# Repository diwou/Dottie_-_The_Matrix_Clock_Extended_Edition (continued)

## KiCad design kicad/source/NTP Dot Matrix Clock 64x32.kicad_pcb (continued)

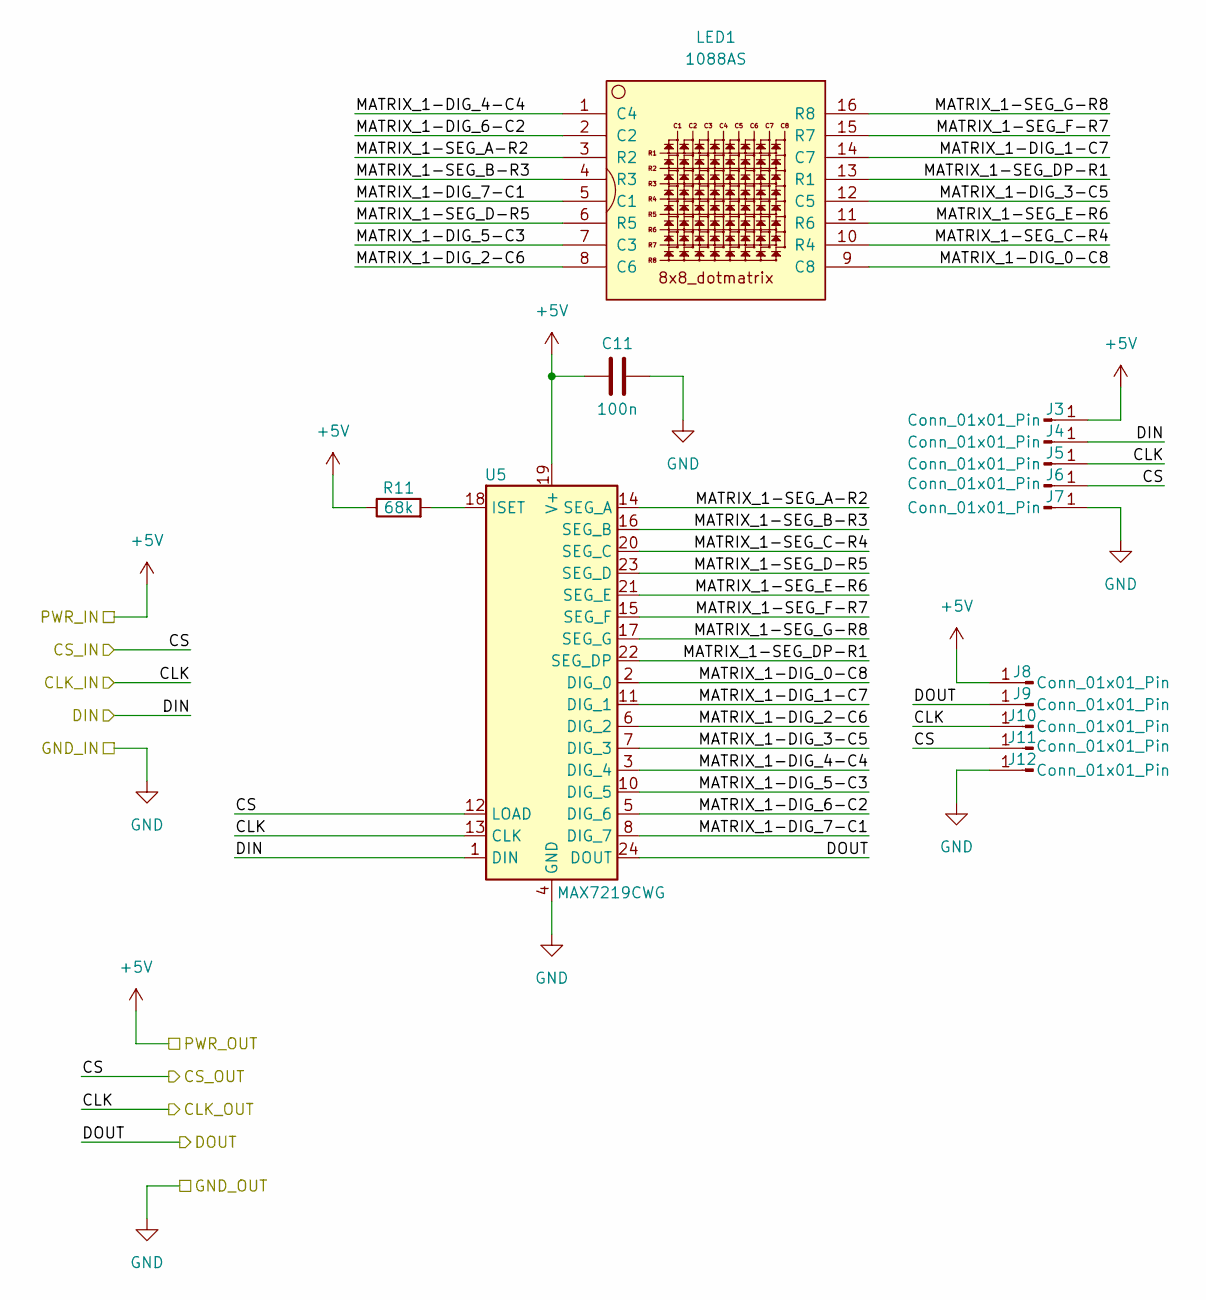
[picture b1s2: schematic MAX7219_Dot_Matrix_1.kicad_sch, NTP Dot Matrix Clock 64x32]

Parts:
C11: 100n; C_0805_2012Metric_Pad1.18x1.45mm_HandSolder
J3, J4, J5, J6, J7, J8, J9, J10, J11, J12: Conn_01x01_Pin; TestPoint_Pad_1.5x1.5mm
LED1: 1088AS; LED_1088_Pin_Header
R11: 68k; R_0805_2012Metric_Pad1.20x1.40mm_HandSolder
U5: MAX7219CWG; SOIC-24W_7.5x15.4mm_P1.27mm

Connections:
+5V: C11.1, J3.1 (Pin_1_1), J8.1 (Pin_1_1), R11.1, U5.19 (V+); also elsewhere on the board
/MAX7219 Dot Matrix 1/DOUT: J9.1 (Pin_1_1), U5.24 (DOUT); also elsewhere on the board
/MAX7219 Dot Matrix 1/MATRIX_1-DIG_0-C8: LED1.9 (C8), U5.2 (DIG_0)
/MAX7219 Dot Matrix 1/MATRIX_1-DIG_1-C7: LED1.14 (C7), U5.11 (DIG_1)
/MAX7219 Dot Matrix 1/MATRIX_1-DIG_2-C6: LED1.8 (C6), U5.6 (DIG_2)
/MAX7219 Dot Matrix 1/MATRIX_1-DIG_3-C5: LED1.12 (C5), U5.7 (DIG_3)
/MAX7219 Dot Matrix 1/MATRIX_1-DIG_4-C4: LED1.1 (C4), U5.3 (DIG_4)
/MAX7219 Dot Matrix 1/MATRIX_1-DIG_5-C3: LED1.7 (C3), U5.10 (DIG_5)
/MAX7219 Dot Matrix 1/MATRIX_1-DIG_6-C2: LED1.2 (C2), U5.5 (DIG_6)
/MAX7219 Dot Matrix 1/MATRIX_1-DIG_7-C1: LED1.5 (C1), U5.8 (DIG_7)
/MAX7219 Dot Matrix 1/MATRIX_1-SEG_A-R2: LED1.3 (R2), U5.14 (SEG_A)
/MAX7219 Dot Matrix 1/MATRIX_1-SEG_B-R3: LED1.4 (R3), U5.16 (SEG_B)
/MAX7219 Dot Matrix 1/MATRIX_1-SEG_C-R4: LED1.10 (R4), U5.20 (SEG_C)
/MAX7219 Dot Matrix 1/MATRIX_1-SEG_D-R5: LED1.6 (R5), U5.23 (SEG_D)
/MAX7219 Dot Matrix 1/MATRIX_1-SEG_DP-R1: LED1.13 (R1), U5.22 (SEG_DP)
/MAX7219 Dot Matrix 1/MATRIX_1-SEG_E-R6: LED1.11 (R6), U5.21 (SEG_E)
/MAX7219 Dot Matrix 1/MATRIX_1-SEG_F-R7: LED1.15 (R7), U5.15 (SEG_F)
/MAX7219 Dot Matrix 1/MATRIX_1-SEG_G-R8: LED1.16 (R8), U5.17 (SEG_G)
CLK: J5.1 (Pin_1_1), J10.1 (Pin_1_1), U5.13 (CLK); also elsewhere on the board
CS: J6.1 (Pin_1_1), J11.1 (Pin_1_1), U5.12 (LOAD); also elsewhere on the board
DIN: J4.1 (Pin_1_1), U5.1 (DIN); also elsewhere on the board
GND: C11.2, J7.1 (Pin_1_1), J12.1 (Pin_1_1), U5.4 (GND), U5.9 (GND); also elsewhere on the board
unnamed: R11.2, U5.18 (ISET)

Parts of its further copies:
C12, C13, C14, C15, C16, C17, C18, C19, C20, C21, C22, C23, C24, C25, C26, C27, C28, C29, C30, C31, C32, C33, C34: 100n; C_0805_2012Metric_Pad1.18x1.45mm_HandSolder
J13, J14, J15, J16, J17, J18, J19, J20, J21, J22, J23, J24, J25, J26, J27, J28, J29, J30, J31, J32, J33, J34, J35, J36, J37, J38, J39, J40, J41, J42, J43, J44, J45, J46, J47, J48, J49, J50, J51, J52, J53, J54, J55, J56, J57, J58, J59, J60, J61, J62, J63, J64, J65, J66, J67, J68, J69, J70, J71, J72, J73, J74, J75, J76, J77, J78, J79, J80, J81, J82, J83, J84, J85, J86, J87, J88, J89, J90, J91, J92, J93, J94, J95, J96, J97, J98, J99, J100, J101, J102, J103, J104, J105, J106, J107, J108, J109, J110, J111, J112, J113, J114, J115, J116, J117, J118, J119, J120, J121, J122, J123, J124, J125, J126, J127, J128, J129, J130, J131, J132, J133, J134, J135, J136, J137, J138, J139, J140, J141, J142, J143, J144, J145, J146, J147, J148, J149, J150, J151, J152, J153, J154, J155, J156, J157, J158, J159, J160, J161, J162, J163, J164, J165, J166, J167, J168, J169, J170, J171, J172, J173, J174, J175, J176, J177, J178, J179, J180, J181, J182, J183, J184, J185, J186, J187, J188, J189, J190, J191, J192, J193, J194, J195, J196, J197, J198, J199, J200, J201, J202, J203, J204, J205, J206, J207, J208, J209, J210, J211, J212, J213, J214, J215, J216, J217, J218, J219, J220, J221, J222, J223, J224, J225, J226, J227, J228, J229, J230, J231, J232, J233, J234, J235, J236, J237, J238, J239, J240, J241, J242: Conn_01x01_Pin; TestPoint_Pad_1.5x1.5mm
LED2, LED3, LED4, LED5, LED6, LED7, LED8, LED9, LED10, LED11, LED12, LED13, LED14, LED15, LED16, LED17, LED18, LED19, LED20, LED21, LED22, LED23, LED24: 1088AS; LED_1088_Pin_Header
R12, R13, R14, R15, R16, R17, R18, R19, R20, R21, R22, R23, R24, R25, R26, R27, R28, R29, R30, R31, R32, R33, R34: 68k; R_0805_2012Metric_Pad1.20x1.40mm_HandSolder
U6, U7, U8, U9, U10, U11, U12, U13, U14, U15, U16, U17, U18, U19, U20, U21, U22, U23, U24, U25, U26, U27, U28: MAX7219CWG; SOIC-24W_7.5x15.4mm_P1.27mm

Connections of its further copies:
+5V: C12.1, C13.1, C14.1, C15.1, C16.1, C17.1, C18.1, C19.1, C20.1, C21.1, C22.1, C23.1, C24.1, C25.1, C26.1, C27.1, C28.1, C29.1, C30.1, C31.1, C32.1, C33.1, C34.1, J13.1 (Pin_1_1), J18.1 (Pin_1_1), J23.1 (Pin_1_1), J28.1 (Pin_1_1), J33.1 (Pin_1_1), J38.1 (Pin_1_1), J43.1 (Pin_1_1), J48.1 (Pin_1_1), J53.1 (Pin_1_1), J58.1 (Pin_1_1), J63.1 (Pin_1_1), J68.1 (Pin_1_1), J73.1 (Pin_1_1), J78.1 (Pin_1_1), J83.1 (Pin_1_1), J88.1 (Pin_1_1), J93.1 (Pin_1_1), J98.1 (Pin_1_1), J103.1 (Pin_1_1), J108.1 (Pin_1_1), J113.1 (Pin_1_1), J118.1 (Pin_1_1), J123.1 (Pin_1_1), J128.1 (Pin_1_1), J133.1 (Pin_1_1), J138.1 (Pin_1_1), J143.1 (Pin_1_1), J148.1 (Pin_1_1), J153.1 (Pin_1_1), J158.1 (Pin_1_1), J163.1 (Pin_1_1), J168.1 (Pin_1_1), J173.1 (Pin_1_1), J178.1 (Pin_1_1), J183.1 (Pin_1_1), J188.1 (Pin_1_1), J193.1 (Pin_1_1), J198.1 (Pin_1_1), J203.1 (Pin_1_1), J208.1 (Pin_1_1), J213.1 (Pin_1_1), J218.1 (Pin_1_1), J223.1 (Pin_1_1), J228.1 (Pin_1_1), J233.1 (Pin_1_1), J238.1 (Pin_1_1), R12.1, R13.1, R14.1, R15.1, R16.1, R17.1, R18.1, R19.1, R20.1, R21.1, R22.1, R23.1, R24.1, R25.1, R26.1, R27.1, R28.1, R29.1, R30.1, R31.1, R32.1, R33.1, R34.1, U6.19 (V+), U7.19 (V+), U8.19 (V+)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; also elsewhere on the board
/MAX7219 Dot Matrix 1/DOUT: J14.1 (Pin_1_1), U6.1 (DIN); also elsewhere on the board
/MAX7219 Dot Matrix 2/DOUT: J19.1 (Pin_1_1), J24.1 (Pin_1_1), U6.24 (DOUT), U7.1 (DIN)
/MAX7219 Dot Matrix 2/MATRIX_1-DIG_0-C8: LED2.9 (C8), U6.2 (DIG_0)
/MAX7219 Dot Matrix 2/MATRIX_1-DIG_1-C7: LED2.14 (C7), U6.11 (DIG_1)
/MAX7219 Dot Matrix 2/MATRIX_1-DIG_2-C6: LED2.8 (C6), U6.6 (DIG_2)
/MAX7219 Dot Matrix 2/MATRIX_1-DIG_3-C5: LED2.12 (C5), U6.7 (DIG_3)
/MAX7219 Dot Matrix 2/MATRIX_1-DIG_4-C4: LED2.1 (C4), U6.3 (DIG_4)
/MAX7219 Dot Matrix 2/MATRIX_1-DIG_5-C3: LED2.7 (C3), U6.10 (DIG_5)
/MAX7219 Dot Matrix 2/MATRIX_1-DIG_6-C2: LED2.2 (C2), U6.5 (DIG_6)
/MAX7219 Dot Matrix 2/MATRIX_1-DIG_7-C1: LED2.5 (C1), U6.8 (DIG_7)
/MAX7219 Dot Matrix 2/MATRIX_1-SEG_A-R2: LED2.3 (R2), U6.14 (SEG_A)
/MAX7219 Dot Matrix 2/MATRIX_1-SEG_B-R3: LED2.4 (R3), U6.16 (SEG_B)
/MAX7219 Dot Matrix 2/MATRIX_1-SEG_C-R4: LED2.10 (R4), U6.20 (SEG_C)
/MAX7219 Dot Matrix 2/MATRIX_1-SEG_D-R5: LED2.6 (R5), U6.23 (SEG_D)
/MAX7219 Dot Matrix 2/MATRIX_1-SEG_DP-R1: LED2.13 (R1), U6.22 (SEG_DP)
/MAX7219 Dot Matrix 2/MATRIX_1-SEG_E-R6: LED2.11 (R6), U6.21 (SEG_E)
/MAX7219 Dot Matrix 2/MATRIX_1-SEG_F-R7: LED2.15 (R7), U6.15 (SEG_F)
/MAX7219 Dot Matrix 2/MATRIX_1-SEG_G-R8: LED2.16 (R8), U6.17 (SEG_G)
/MAX7219 Dot Matrix 3/DOUT: J29.1 (Pin_1_1), J34.1 (Pin_1_1), U7.24 (DOUT), U8.1 (DIN)
/MAX7219 Dot Matrix 3/MATRIX_1-DIG_0-C8: LED3.9 (C8), U7.2 (DIG_0)
/MAX7219 Dot Matrix 3/MATRIX_1-DIG_1-C7: LED3.14 (C7), U7.11 (DIG_1)
/MAX7219 Dot Matrix 3/MATRIX_1-DIG_2-C6: LED3.8 (C6), U7.6 (DIG_2)
/MAX7219 Dot Matrix 3/MATRIX_1-DIG_3-C5: LED3.12 (C5), U7.7 (DIG_3)
/MAX7219 Dot Matrix 3/MATRIX_1-DIG_4-C4: LED3.1 (C4), U7.3 (DIG_4)
/MAX7219 Dot Matrix 3/MATRIX_1-DIG_5-C3: LED3.7 (C3), U7.10 (DIG_5)
/MAX7219 Dot Matrix 3/MATRIX_1-DIG_6-C2: LED3.2 (C2), U7.5 (DIG_6)
/MAX7219 Dot Matrix 3/MATRIX_1-DIG_7-C1: LED3.5 (C1), U7.8 (DIG_7)
/MAX7219 Dot Matrix 3/MATRIX_1-SEG_A-R2: LED3.3 (R2), U7.14 (SEG_A)
/MAX7219 Dot Matrix 3/MATRIX_1-SEG_B-R3: LED3.4 (R3), U7.16 (SEG_B)
/MAX7219 Dot Matrix 3/MATRIX_1-SEG_C-R4: LED3.10 (R4), U7.20 (SEG_C)
/MAX7219 Dot Matrix 3/MATRIX_1-SEG_D-R5: LED3.6 (R5), U7.23 (SEG_D)
/MAX7219 Dot Matrix 3/MATRIX_1-SEG_DP-R1: LED3.13 (R1), U7.22 (SEG_DP)
/MAX7219 Dot Matrix 3/MATRIX_1-SEG_E-R6: LED3.11 (R6), U7.21 (SEG_E)
/MAX7219 Dot Matrix 3/MATRIX_1-SEG_F-R7: LED3.15 (R7), U7.15 (SEG_F)
/MAX7219 Dot Matrix 3/MATRIX_1-SEG_G-R8: LED3.16 (R8), U7.17 (SEG_G)
/MAX7219 Dot Matrix 4/DOUT: J39.1 (Pin_1_1), J44.1 (Pin_1_1), U8.24 (DOUT), U9.1 (DIN)
/MAX7219 Dot Matrix 4/MATRIX_1-DIG_0-C8: LED4.9 (C8), U8.2 (DIG_0)
/MAX7219 Dot Matrix 4/MATRIX_1-DIG_1-C7: LED4.14 (C7), U8.11 (DIG_1)
/MAX7219 Dot Matrix 4/MATRIX_1-DIG_2-C6: LED4.8 (C6), U8.6 (DIG_2)
/MAX7219 Dot Matrix 4/MATRIX_1-DIG_3-C5: LED4.12 (C5), U8.7 (DIG_3)
/MAX7219 Dot Matrix 4/MATRIX_1-DIG_4-C4: LED4.1 (C4), U8.3 (DIG_4)
/MAX7219 Dot Matrix 4/MATRIX_1-DIG_5-C3: LED4.7 (C3), U8.10 (DIG_5)
/MAX7219 Dot Matrix 4/MATRIX_1-DIG_6-C2: LED4.2 (C2), U8.5 (DIG_6)
/MAX7219 Dot Matrix 4/MATRIX_1-DIG_7-C1: LED4.5 (C1), U8.8 (DIG_7)
/MAX7219 Dot Matrix 4/MATRIX_1-SEG_A-R2: LED4.3 (R2), U8.14 (SEG_A)
/MAX7219 Dot Matrix 4/MATRIX_1-SEG_B-R3: LED4.4 (R3), U8.16 (SEG_B)
/MAX7219 Dot Matrix 4/MATRIX_1-SEG_C-R4: LED4.10 (R4), U8.20 (SEG_C)
/MAX7219 Dot Matrix 4/MATRIX_1-SEG_D-R5: LED4.6 (R5), U8.23 (SEG_D)
/MAX7219 Dot Matrix 4/MATRIX_1-SEG_DP-R1: LED4.13 (R1), U8.22 (SEG_DP)
/MAX7219 Dot Matrix 4/MATRIX_1-SEG_E-R6: LED4.11 (R6), U8.21 (SEG_E)
/MAX7219 Dot Matrix 4/MATRIX_1-SEG_F-R7: LED4.15 (R7), U8.15 (SEG_F)
/MAX7219 Dot Matrix 4/MATRIX_1-SEG_G-R8: LED4.16 (R8), U8.17 (SEG_G)
/MAX7219 Dot Matrix 5/DOUT: J49.1 (Pin_1_1), J54.1 (Pin_1_1), U9.24 (DOUT), U10.1 (DIN)
/MAX7219 Dot Matrix 5/MATRIX_1-DIG_0-C8: LED5.9 (C8), U9.2 (DIG_0)
/MAX7219 Dot Matrix 5/MATRIX_1-DIG_1-C7: LED5.14 (C7), U9.11 (DIG_1)
/MAX7219 Dot Matrix 5/MATRIX_1-DIG_2-C6: LED5.8 (C6), U9.6 (DIG_2)
/MAX7219 Dot Matrix 5/MATRIX_1-DIG_3-C5: LED5.12 (C5), U9.7 (DIG_3)
/MAX7219 Dot Matrix 5/MATRIX_1-DIG_4-C4: LED5.1 (C4), U9.3 (DIG_4)
/MAX7219 Dot Matrix 5/MATRIX_1-DIG_5-C3: LED5.7 (C3), U9.10 (DIG_5)
/MAX7219 Dot Matrix 5/MATRIX_1-DIG_6-C2: LED5.2 (C2), U9.5 (DIG_6)
/MAX7219 Dot Matrix 5/MATRIX_1-DIG_7-C1: LED5.5 (C1), U9.8 (DIG_7)
/MAX7219 Dot Matrix 5/MATRIX_1-SEG_A-R2: LED5.3 (R2), U9.14 (SEG_A)
/MAX7219 Dot Matrix 5/MATRIX_1-SEG_B-R3: LED5.4 (R3), U9.16 (SEG_B)
/MAX7219 Dot Matrix 5/MATRIX_1-SEG_C-R4: LED5.10 (R4), U9.20 (SEG_C)
/MAX7219 Dot Matrix 5/MATRIX_1-SEG_D-R5: LED5.6 (R5), U9.23 (SEG_D)
/MAX7219 Dot Matrix 5/MATRIX_1-SEG_DP-R1: LED5.13 (R1), U9.22 (SEG_DP)
/MAX7219 Dot Matrix 5/MATRIX_1-SEG_E-R6: LED5.11 (R6), U9.21 (SEG_E)
/MAX7219 Dot Matrix 5/MATRIX_1-SEG_F-R7: LED5.15 (R7), U9.15 (SEG_F)
/MAX7219 Dot Matrix 5/MATRIX_1-SEG_G-R8: LED5.16 (R8), U9.17 (SEG_G)
/MAX7219 Dot Matrix 6/DOUT: J59.1 (Pin_1_1), J64.1 (Pin_1_1), U10.24 (DOUT), U11.1 (DIN)
/MAX7219 Dot Matrix 6/MATRIX_1-DIG_0-C8: LED6.9 (C8), U10.2 (DIG_0)
/MAX7219 Dot Matrix 6/MATRIX_1-DIG_1-C7: LED6.14 (C7), U10.11 (DIG_1)
/MAX7219 Dot Matrix 6/MATRIX_1-DIG_2-C6: LED6.8 (C6), U10.6 (DIG_2)
/MAX7219 Dot Matrix 6/MATRIX_1-DIG_3-C5: LED6.12 (C5), U10.7 (DIG_3)
/MAX7219 Dot Matrix 6/MATRIX_1-DIG_4-C4: LED6.1 (C4), U10.3 (DIG_4)
/MAX7219 Dot Matrix 6/MATRIX_1-DIG_5-C3: LED6.7 (C3), U10.10 (DIG_5)
/MAX7219 Dot Matrix 6/MATRIX_1-DIG_6-C2: LED6.2 (C2), U10.5 (DIG_6)
/MAX7219 Dot Matrix 6/MATRIX_1-DIG_7-C1: LED6.5 (C1), U10.8 (DIG_7)
/MAX7219 Dot Matrix 6/MATRIX_1-SEG_A-R2: LED6.3 (R2), U10.14 (SEG_A)
/MAX7219 Dot Matrix 6/MATRIX_1-SEG_B-R3: LED6.4 (R3), U10.16 (SEG_B)
/MAX7219 Dot Matrix 6/MATRIX_1-SEG_C-R4: LED6.10 (R4), U10.20 (SEG_C)
/MAX7219 Dot Matrix 6/MATRIX_1-SEG_D-R5: LED6.6 (R5), U10.23 (SEG_D)
/MAX7219 Dot Matrix 6/MATRIX_1-SEG_DP-R1: LED6.13 (R1), U10.22 (SEG_DP)
/MAX7219 Dot Matrix 6/MATRIX_1-SEG_E-R6: LED6.11 (R6), U10.21 (SEG_E)
/MAX7219 Dot Matrix 6/MATRIX_1-SEG_F-R7: LED6.15 (R7), U10.15 (SEG_F)
/MAX7219 Dot Matrix 6/MATRIX_1-SEG_G-R8: LED6.16 (R8), U10.17 (SEG_G)
/MAX7219 Dot Matrix 7/DOUT: J69.1 (Pin_1_1), J74.1 (Pin_1_1), U11.24 (DOUT), U12.1 (DIN)
/MAX7219 Dot Matrix 7/MATRIX_1-DIG_0-C8: LED7.9 (C8), U11.2 (DIG_0)
/MAX7219 Dot Matrix 7/MATRIX_1-DIG_1-C7: LED7.14 (C7), U11.11 (DIG_1)
/MAX7219 Dot Matrix 7/MATRIX_1-DIG_2-C6: LED7.8 (C6), U11.6 (DIG_2)
/MAX7219 Dot Matrix 7/MATRIX_1-DIG_3-C5: LED7.12 (C5), U11.7 (DIG_3)
/MAX7219 Dot Matrix 7/MATRIX_1-DIG_4-C4: LED7.1 (C4), U11.3 (DIG_4)
/MAX7219 Dot Matrix 7/MATRIX_1-DIG_5-C3: LED7.7 (C3), U11.10 (DIG_5)
/MAX7219 Dot Matrix 7/MATRIX_1-DIG_6-C2: LED7.2 (C2), U11.5 (DIG_6)
/MAX7219 Dot Matrix 7/MATRIX_1-DIG_7-C1: LED7.5 (C1), U11.8 (DIG_7)
/MAX7219 Dot Matrix 7/MATRIX_1-SEG_A-R2: LED7.3 (R2), U11.14 (SEG_A)
/MAX7219 Dot Matrix 7/MATRIX_1-SEG_B-R3: LED7.4 (R3), U11.16 (SEG_B)
/MAX7219 Dot Matrix 7/MATRIX_1-SEG_C-R4: LED7.10 (R4), U11.20 (SEG_C)
/MAX7219 Dot Matrix 7/MATRIX_1-SEG_D-R5: LED7.6 (R5), U11.23 (SEG_D)
/MAX7219 Dot Matrix 7/MATRIX_1-SEG_DP-R1: LED7.13 (R1), U11.22 (SEG_DP)
/MAX7219 Dot Matrix 7/MATRIX_1-SEG_E-R6: LED7.11 (R6), U11.21 (SEG_E)
/MAX7219 Dot Matrix 7/MATRIX_1-SEG_F-R7: LED7.15 (R7), U11.15 (SEG_F)
/MAX7219 Dot Matrix 7/MATRIX_1-SEG_G-R8: LED7.16 (R8), U11.17 (SEG_G)
/MAX7219 Dot Matrix 8/DOUT: J79.1 (Pin_1_1), J84.1 (Pin_1_1), U12.24 (DOUT), U13.1 (DIN)
/MAX7219 Dot Matrix 8/MATRIX_1-DIG_0-C8: LED8.9 (C8), U12.2 (DIG_0)
/MAX7219 Dot Matrix 8/MATRIX_1-DIG_1-C7: LED8.14 (C7), U12.11 (DIG_1)
/MAX7219 Dot Matrix 8/MATRIX_1-DIG_2-C6: LED8.8 (C6), U12.6 (DIG_2)
/MAX7219 Dot Matrix 8/MATRIX_1-DIG_3-C5: LED8.12 (C5), U12.7 (DIG_3)
/MAX7219 Dot Matrix 8/MATRIX_1-DIG_4-C4: LED8.1 (C4), U12.3 (DIG_4)
/MAX7219 Dot Matrix 8/MATRIX_1-DIG_5-C3: LED8.7 (C3), U12.10 (DIG_5)
/MAX7219 Dot Matrix 8/MATRIX_1-DIG_6-C2: LED8.2 (C2), U12.5 (DIG_6)
/MAX7219 Dot Matrix 8/MATRIX_1-DIG_7-C1: LED8.5 (C1), U12.8 (DIG_7)
/MAX7219 Dot Matrix 8/MATRIX_1-SEG_A-R2: LED8.3 (R2), U12.14 (SEG_A)
/MAX7219 Dot Matrix 8/MATRIX_1-SEG_B-R3: LED8.4 (R3), U12.16 (SEG_B)
/MAX7219 Dot Matrix 8/MATRIX_1-SEG_C-R4: LED8.10 (R4), U12.20 (SEG_C)
/MAX7219 Dot Matrix 8/MATRIX_1-SEG_D-R5: LED8.6 (R5), U12.23 (SEG_D)
/MAX7219 Dot Matrix 8/MATRIX_1-SEG_DP-R1: LED8.13 (R1), U12.22 (SEG_DP)
/MAX7219 Dot Matrix 8/MATRIX_1-SEG_E-R6: LED8.11 (R6), U12.21 (SEG_E)
/MAX7219 Dot Matrix 8/MATRIX_1-SEG_F-R7: LED8.15 (R7), U12.15 (SEG_F)
/MAX7219 Dot Matrix 8/MATRIX_1-SEG_G-R8: LED8.16 (R8), U12.17 (SEG_G)
/MAX7219 Dot Matrix 9/MATRIX_1-DIG_0-C8: LED9.9 (C8), U13.2 (DIG_0)
/MAX7219 Dot Matrix 9/MATRIX_1-DIG_1-C7: LED9.14 (C7), U13.11 (DIG_1)
/MAX7219 Dot Matrix 9/MATRIX_1-DIG_2-C6: LED9.8 (C6), U13.6 (DIG_2)
/MAX7219 Dot Matrix 9/MATRIX_1-DIG_3-C5: LED9.12 (C5), U13.7 (DIG_3)
/MAX7219 Dot Matrix 9/MATRIX_1-DIG_4-C4: LED9.1 (C4), U13.3 (DIG_4)
/MAX7219 Dot Matrix 9/MATRIX_1-DIG_5-C3: LED9.7 (C3), U13.10 (DIG_5)
/MAX7219 Dot Matrix 9/MATRIX_1-DIG_6-C2: LED9.2 (C2), U13.5 (DIG_6)
/MAX7219 Dot Matrix 9/MATRIX_1-DIG_7-C1: LED9.5 (C1), U13.8 (DIG_7)
/MAX7219 Dot Matrix 9/MATRIX_1-SEG_A-R2: LED9.3 (R2), U13.14 (SEG_A)
/MAX7219 Dot Matrix 9/MATRIX_1-SEG_B-R3: LED9.4 (R3), U13.16 (SEG_B)
/MAX7219 Dot Matrix 9/MATRIX_1-SEG_C-R4: LED9.10 (R4), U13.20 (SEG_C)
/MAX7219 Dot Matrix 9/MATRIX_1-SEG_D-R5: LED9.6 (R5), U13.23 (SEG_D)
/MAX7219 Dot Matrix 9/MATRIX_1-SEG_DP-R1: LED9.13 (R1), U13.22 (SEG_DP)
/MAX7219 Dot Matrix 9/MATRIX_1-SEG_E-R6: LED9.11 (R6), U13.21 (SEG_E)
/MAX7219 Dot Matrix 9/MATRIX_1-SEG_F-R7: LED9.15 (R7), U13.15 (SEG_F)
/MAX7219 Dot Matrix 9/MATRIX_1-SEG_G-R8: LED9.16 (R8), U13.17 (SEG_G)
/MAX7219 Dot Matrix 10/DIN: J89.1 (Pin_1_1), J94.1 (Pin_1_1), U13.24 (DOUT), U14.1 (DIN)
/MAX7219 Dot Matrix 10/DOUT: J99.1 (Pin_1_1), J104.1 (Pin_1_1), U14.24 (DOUT), U15.1 (DIN)
/MAX7219 Dot Matrix 10/MATRIX_1-DIG_0-C8: LED10.9 (C8), U14.2 (DIG_0)
/MAX7219 Dot Matrix 10/MATRIX_1-DIG_1-C7: LED10.14 (C7), U14.11 (DIG_1)
/MAX7219 Dot Matrix 10/MATRIX_1-DIG_2-C6: LED10.8 (C6), U14.6 (DIG_2)
/MAX7219 Dot Matrix 10/MATRIX_1-DIG_3-C5: LED10.12 (C5), U14.7 (DIG_3)
/MAX7219 Dot Matrix 10/MATRIX_1-DIG_4-C4: LED10.1 (C4), U14.3 (DIG_4)
/MAX7219 Dot Matrix 10/MATRIX_1-DIG_5-C3: LED10.7 (C3), U14.10 (DIG_5)
/MAX7219 Dot Matrix 10/MATRIX_1-DIG_6-C2: LED10.2 (C2), U14.5 (DIG_6)
/MAX7219 Dot Matrix 10/MATRIX_1-DIG_7-C1: LED10.5 (C1), U14.8 (DIG_7)
/MAX7219 Dot Matrix 10/MATRIX_1-SEG_A-R2: LED10.3 (R2), U14.14 (SEG_A)
/MAX7219 Dot Matrix 10/MATRIX_1-SEG_B-R3: LED10.4 (R3), U14.16 (SEG_B)
/MAX7219 Dot Matrix 10/MATRIX_1-SEG_C-R4: LED10.10 (R4), U14.20 (SEG_C)
/MAX7219 Dot Matrix 10/MATRIX_1-SEG_D-R5: LED10.6 (R5), U14.23 (SEG_D)
/MAX7219 Dot Matrix 10/MATRIX_1-SEG_DP-R1: LED10.13 (R1), U14.22 (SEG_DP)
/MAX7219 Dot Matrix 10/MATRIX_1-SEG_E-R6: LED10.11 (R6), U14.21 (SEG_E)
/MAX7219 Dot Matrix 10/MATRIX_1-SEG_F-R7: LED10.15 (R7), U14.15 (SEG_F)
/MAX7219 Dot Matrix 10/MATRIX_1-SEG_G-R8: LED10.16 (R8), U14.17 (SEG_G)
/MAX7219 Dot Matrix 11/DOUT: J109.1 (Pin_1_1), J114.1 (Pin_1_1), U15.24 (DOUT), U16.1 (DIN)
/MAX7219 Dot Matrix 11/MATRIX_1-DIG_0-C8: LED11.9 (C8), U15.2 (DIG_0)
/MAX7219 Dot Matrix 11/MATRIX_1-DIG_1-C7: LED11.14 (C7), U15.11 (DIG_1)
/MAX7219 Dot Matrix 11/MATRIX_1-DIG_2-C6: LED11.8 (C6), U15.6 (DIG_2)
/MAX7219 Dot Matrix 11/MATRIX_1-DIG_3-C5: LED11.12 (C5), U15.7 (DIG_3)
/MAX7219 Dot Matrix 11/MATRIX_1-DIG_4-C4: LED11.1 (C4), U15.3 (DIG_4)
/MAX7219 Dot Matrix 11/MATRIX_1-DIG_5-C3: LED11.7 (C3), U15.10 (DIG_5)
/MAX7219 Dot Matrix 11/MATRIX_1-DIG_6-C2: LED11.2 (C2), U15.5 (DIG_6)
/MAX7219 Dot Matrix 11/MATRIX_1-DIG_7-C1: LED11.5 (C1), U15.8 (DIG_7)
/MAX7219 Dot Matrix 11/MATRIX_1-SEG_A-R2: LED11.3 (R2), U15.14 (SEG_A)
/MAX7219 Dot Matrix 11/MATRIX_1-SEG_B-R3: LED11.4 (R3), U15.16 (SEG_B)
/MAX7219 Dot Matrix 11/MATRIX_1-SEG_C-R4: LED11.10 (R4), U15.20 (SEG_C)
/MAX7219 Dot Matrix 11/MATRIX_1-SEG_D-R5: LED11.6 (R5), U15.23 (SEG_D)
/MAX7219 Dot Matrix 11/MATRIX_1-SEG_DP-R1: LED11.13 (R1), U15.22 (SEG_DP)
/MAX7219 Dot Matrix 11/MATRIX_1-SEG_E-R6: LED11.11 (R6), U15.21 (SEG_E)
/MAX7219 Dot Matrix 11/MATRIX_1-SEG_F-R7: LED11.15 (R7), U15.15 (SEG_F)
/MAX7219 Dot Matrix 11/MATRIX_1-SEG_G-R8: LED11.16 (R8), U15.17 (SEG_G)
/MAX7219 Dot Matrix 12/DOUT: J119.1 (Pin_1_1), J124.1 (Pin_1_1), U16.24 (DOUT), U17.1 (DIN)
/MAX7219 Dot Matrix 12/MATRIX_1-DIG_0-C8: LED12.9 (C8), U16.2 (DIG_0)
/MAX7219 Dot Matrix 12/MATRIX_1-DIG_1-C7: LED12.14 (C7), U16.11 (DIG_1)
/MAX7219 Dot Matrix 12/MATRIX_1-DIG_2-C6: LED12.8 (C6), U16.6 (DIG_2)
/MAX7219 Dot Matrix 12/MATRIX_1-DIG_3-C5: LED12.12 (C5), U16.7 (DIG_3)
/MAX7219 Dot Matrix 12/MATRIX_1-DIG_4-C4: LED12.1 (C4), U16.3 (DIG_4)
/MAX7219 Dot Matrix 12/MATRIX_1-DIG_5-C3: LED12.7 (C3), U16.10 (DIG_5)
/MAX7219 Dot Matrix 12/MATRIX_1-DIG_6-C2: LED12.2 (C2), U16.5 (DIG_6)
/MAX7219 Dot Matrix 12/MATRIX_1-DIG_7-C1: LED12.5 (C1), U16.8 (DIG_7)
/MAX7219 Dot Matrix 12/MATRIX_1-SEG_A-R2: LED12.3 (R2), U16.14 (SEG_A)
/MAX7219 Dot Matrix 12/MATRIX_1-SEG_B-R3: LED12.4 (R3), U16.16 (SEG_B)
/MAX7219 Dot Matrix 12/MATRIX_1-SEG_C-R4: LED12.10 (R4), U16.20 (SEG_C)
/MAX7219 Dot Matrix 12/MATRIX_1-SEG_D-R5: LED12.6 (R5), U16.23 (SEG_D)
/MAX7219 Dot Matrix 12/MATRIX_1-SEG_DP-R1: LED12.13 (R1), U16.22 (SEG_DP)
/MAX7219 Dot Matrix 12/MATRIX_1-SEG_E-R6: LED12.11 (R6), U16.21 (SEG_E)
/MAX7219 Dot Matrix 12/MATRIX_1-SEG_F-R7: LED12.15 (R7), U16.15 (SEG_F)
/MAX7219 Dot Matrix 12/MATRIX_1-SEG_G-R8: LED12.16 (R8), U16.17 (SEG_G)
/MAX7219 Dot Matrix 13/DOUT: J129.1 (Pin_1_1), J134.1 (Pin_1_1), U17.24 (DOUT), U18.1 (DIN)
/MAX7219 Dot Matrix 13/MATRIX_1-DIG_0-C8: LED13.9 (C8), U17.2 (DIG_0)
/MAX7219 Dot Matrix 13/MATRIX_1-DIG_1-C7: LED13.14 (C7), U17.11 (DIG_1)
/MAX7219 Dot Matrix 13/MATRIX_1-DIG_2-C6: LED13.8 (C6), U17.6 (DIG_2)
/MAX7219 Dot Matrix 13/MATRIX_1-DIG_3-C5: LED13.12 (C5), U17.7 (DIG_3)
/MAX7219 Dot Matrix 13/MATRIX_1-DIG_4-C4: LED13.1 (C4), U17.3 (DIG_4)
/MAX7219 Dot Matrix 13/MATRIX_1-DIG_5-C3: LED13.7 (C3), U17.10 (DIG_5)
/MAX7219 Dot Matrix 13/MATRIX_1-DIG_6-C2: LED13.2 (C2), U17.5 (DIG_6)
/MAX7219 Dot Matrix 13/MATRIX_1-DIG_7-C1: LED13.5 (C1), U17.8 (DIG_7)
/MAX7219 Dot Matrix 13/MATRIX_1-SEG_A-R2: LED13.3 (R2), U17.14 (SEG_A)
/MAX7219 Dot Matrix 13/MATRIX_1-SEG_B-R3: LED13.4 (R3), U17.16 (SEG_B)
/MAX7219 Dot Matrix 13/MATRIX_1-SEG_C-R4: LED13.10 (R4), U17.20 (SEG_C)
/MAX7219 Dot Matrix 13/MATRIX_1-SEG_D-R5: LED13.6 (R5), U17.23 (SEG_D)
/MAX7219 Dot Matrix 13/MATRIX_1-SEG_DP-R1: LED13.13 (R1), U17.22 (SEG_DP)
/MAX7219 Dot Matrix 13/MATRIX_1-SEG_E-R6: LED13.11 (R6), U17.21 (SEG_E)
/MAX7219 Dot Matrix 13/MATRIX_1-SEG_F-R7: LED13.15 (R7), U17.15 (SEG_F)
/MAX7219 Dot Matrix 13/MATRIX_1-SEG_G-R8: LED13.16 (R8), U17.17 (SEG_G)
/MAX7219 Dot Matrix 14/DOUT: J139.1 (Pin_1_1), J144.1 (Pin_1_1), U18.24 (DOUT), U19.1 (DIN)
/MAX7219 Dot Matrix 14/MATRIX_1-DIG_0-C8: LED14.9 (C8), U18.2 (DIG_0)
/MAX7219 Dot Matrix 14/MATRIX_1-DIG_1-C7: LED14.14 (C7), U18.11 (DIG_1)
/MAX7219 Dot Matrix 14/MATRIX_1-DIG_2-C6: LED14.8 (C6), U18.6 (DIG_2)
/MAX7219 Dot Matrix 14/MATRIX_1-DIG_3-C5: LED14.12 (C5), U18.7 (DIG_3)
/MAX7219 Dot Matrix 14/MATRIX_1-DIG_4-C4: LED14.1 (C4), U18.3 (DIG_4)
/MAX7219 Dot Matrix 14/MATRIX_1-DIG_5-C3: LED14.7 (C3), U18.10 (DIG_5)
/MAX7219 Dot Matrix 14/MATRIX_1-DIG_6-C2: LED14.2 (C2), U18.5 (DIG_6)
/MAX7219 Dot Matrix 14/MATRIX_1-DIG_7-C1: LED14.5 (C1), U18.8 (DIG_7)
/MAX7219 Dot Matrix 14/MATRIX_1-SEG_A-R2: LED14.3 (R2), U18.14 (SEG_A)
/MAX7219 Dot Matrix 14/MATRIX_1-SEG_B-R3: LED14.4 (R3), U18.16 (SEG_B)
/MAX7219 Dot Matrix 14/MATRIX_1-SEG_C-R4: LED14.10 (R4), U18.20 (SEG_C)
/MAX7219 Dot Matrix 14/MATRIX_1-SEG_D-R5: LED14.6 (R5), U18.23 (SEG_D)
/MAX7219 Dot Matrix 14/MATRIX_1-SEG_DP-R1: LED14.13 (R1), U18.22 (SEG_DP)
/MAX7219 Dot Matrix 14/MATRIX_1-SEG_E-R6: LED14.11 (R6), U18.21 (SEG_E)
/MAX7219 Dot Matrix 14/MATRIX_1-SEG_F-R7: LED14.15 (R7), U18.15 (SEG_F)
/MAX7219 Dot Matrix 14/MATRIX_1-SEG_G-R8: LED14.16 (R8), U18.17 (SEG_G)
/MAX7219 Dot Matrix 15/DOUT: J149.1 (Pin_1_1), J154.1 (Pin_1_1), U19.24 (DOUT), U20.1 (DIN)
/MAX7219 Dot Matrix 15/MATRIX_1-DIG_0-C8: LED15.9 (C8), U19.2 (DIG_0)
/MAX7219 Dot Matrix 15/MATRIX_1-DIG_1-C7: LED15.14 (C7), U19.11 (DIG_1)
/MAX7219 Dot Matrix 15/MATRIX_1-DIG_2-C6: LED15.8 (C6), U19.6 (DIG_2)
/MAX7219 Dot Matrix 15/MATRIX_1-DIG_3-C5: LED15.12 (C5), U19.7 (DIG_3)
/MAX7219 Dot Matrix 15/MATRIX_1-DIG_4-C4: LED15.1 (C4), U19.3 (DIG_4)
/MAX7219 Dot Matrix 15/MATRIX_1-DIG_5-C3: LED15.7 (C3), U19.10 (DIG_5)
/MAX7219 Dot Matrix 15/MATRIX_1-DIG_6-C2: LED15.2 (C2), U19.5 (DIG_6)
/MAX7219 Dot Matrix 15/MATRIX_1-DIG_7-C1: LED15.5 (C1), U19.8 (DIG_7)
/MAX7219 Dot Matrix 15/MATRIX_1-SEG_A-R2: LED15.3 (R2), U19.14 (SEG_A)
/MAX7219 Dot Matrix 15/MATRIX_1-SEG_B-R3: LED15.4 (R3), U19.16 (SEG_B)
/MAX7219 Dot Matrix 15/MATRIX_1-SEG_C-R4: LED15.10 (R4), U19.20 (SEG_C)
/MAX7219 Dot Matrix 15/MATRIX_1-SEG_D-R5: LED15.6 (R5), U19.23 (SEG_D)
/MAX7219 Dot Matrix 15/MATRIX_1-SEG_DP-R1: LED15.13 (R1), U19.22 (SEG_DP)
/MAX7219 Dot Matrix 15/MATRIX_1-SEG_E-R6: LED15.11 (R6), U19.21 (SEG_E)
/MAX7219 Dot Matrix 15/MATRIX_1-SEG_F-R7: LED15.15 (R7), U19.15 (SEG_F)
/MAX7219 Dot Matrix 15/MATRIX_1-SEG_G-R8: LED15.16 (R8), U19.17 (SEG_G)
/MAX7219 Dot Matrix 16/DOUT: J159.1 (Pin_1_1), J164.1 (Pin_1_1), U20.24 (DOUT), U21.1 (DIN)
/MAX7219 Dot Matrix 16/MATRIX_1-DIG_0-C8: LED16.9 (C8), U20.2 (DIG_0)
/MAX7219 Dot Matrix 16/MATRIX_1-DIG_1-C7: LED16.14 (C7), U20.11 (DIG_1)
/MAX7219 Dot Matrix 16/MATRIX_1-DIG_2-C6: LED16.8 (C6), U20.6 (DIG_2)
/MAX7219 Dot Matrix 16/MATRIX_1-DIG_3-C5: LED16.12 (C5), U20.7 (DIG_3)
/MAX7219 Dot Matrix 16/MATRIX_1-DIG_4-C4: LED16.1 (C4), U20.3 (DIG_4)
/MAX7219 Dot Matrix 16/MATRIX_1-DIG_5-C3: LED16.7 (C3), U20.10 (DIG_5)
/MAX7219 Dot Matrix 16/MATRIX_1-DIG_6-C2: LED16.2 (C2), U20.5 (DIG_6)
/MAX7219 Dot Matrix 16/MATRIX_1-DIG_7-C1: LED16.5 (C1), U20.8 (DIG_7)
/MAX7219 Dot Matrix 16/MATRIX_1-SEG_A-R2: LED16.3 (R2), U20.14 (SEG_A)
/MAX7219 Dot Matrix 16/MATRIX_1-SEG_B-R3: LED16.4 (R3), U20.16 (SEG_B)
/MAX7219 Dot Matrix 16/MATRIX_1-SEG_C-R4: LED16.10 (R4), U20.20 (SEG_C)
/MAX7219 Dot Matrix 16/MATRIX_1-SEG_D-R5: LED16.6 (R5), U20.23 (SEG_D)
/MAX7219 Dot Matrix 16/MATRIX_1-SEG_DP-R1: LED16.13 (R1), U20.22 (SEG_DP)
/MAX7219 Dot Matrix 16/MATRIX_1-SEG_E-R6: LED16.11 (R6), U20.21 (SEG_E)
/MAX7219 Dot Matrix 16/MATRIX_1-SEG_F-R7: LED16.15 (R7), U20.15 (SEG_F)
/MAX7219 Dot Matrix 16/MATRIX_1-SEG_G-R8: LED16.16 (R8), U20.17 (SEG_G)
/MAX7219 Dot Matrix 17/DOUT: J169.1 (Pin_1_1), J174.1 (Pin_1_1), U21.24 (DOUT), U22.1 (DIN)
/MAX7219 Dot Matrix 17/MATRIX_1-DIG_0-C8: LED17.9 (C8), U21.2 (DIG_0)
/MAX7219 Dot Matrix 17/MATRIX_1-DIG_1-C7: LED17.14 (C7), U21.11 (DIG_1)
/MAX7219 Dot Matrix 17/MATRIX_1-DIG_2-C6: LED17.8 (C6), U21.6 (DIG_2)
/MAX7219 Dot Matrix 17/MATRIX_1-DIG_3-C5: LED17.12 (C5), U21.7 (DIG_3)
/MAX7219 Dot Matrix 17/MATRIX_1-DIG_4-C4: LED17.1 (C4), U21.3 (DIG_4)
/MAX7219 Dot Matrix 17/MATRIX_1-DIG_5-C3: LED17.7 (C3), U21.10 (DIG_5)
/MAX7219 Dot Matrix 17/MATRIX_1-DIG_6-C2: LED17.2 (C2), U21.5 (DIG_6)
/MAX7219 Dot Matrix 17/MATRIX_1-DIG_7-C1: LED17.5 (C1), U21.8 (DIG_7)
/MAX7219 Dot Matrix 17/MATRIX_1-SEG_A-R2: LED17.3 (R2), U21.14 (SEG_A)
/MAX7219 Dot Matrix 17/MATRIX_1-SEG_B-R3: LED17.4 (R3), U21.16 (SEG_B)
/MAX7219 Dot Matrix 17/MATRIX_1-SEG_C-R4: LED17.10 (R4), U21.20 (SEG_C)
/MAX7219 Dot Matrix 17/MATRIX_1-SEG_D-R5: LED17.6 (R5), U21.23 (SEG_D)
/MAX7219 Dot Matrix 17/MATRIX_1-SEG_DP-R1: LED17.13 (R1), U21.22 (SEG_DP)
/MAX7219 Dot Matrix 17/MATRIX_1-SEG_E-R6: LED17.11 (R6), U21.21 (SEG_E)
/MAX7219 Dot Matrix 17/MATRIX_1-SEG_F-R7: LED17.15 (R7), U21.15 (SEG_F)
/MAX7219 Dot Matrix 17/MATRIX_1-SEG_G-R8: LED17.16 (R8), U21.17 (SEG_G)
/MAX7219 Dot Matrix 18/DOUT: J179.1 (Pin_1_1), J184.1 (Pin_1_1), U22.24 (DOUT), U23.1 (DIN)
/MAX7219 Dot Matrix 18/MATRIX_1-DIG_0-C8: LED18.9 (C8), U22.2 (DIG_0)
/MAX7219 Dot Matrix 18/MATRIX_1-DIG_1-C7: LED18.14 (C7), U22.11 (DIG_1)
/MAX7219 Dot Matrix 18/MATRIX_1-DIG_2-C6: LED18.8 (C6), U22.6 (DIG_2)
/MAX7219 Dot Matrix 18/MATRIX_1-DIG_3-C5: LED18.12 (C5), U22.7 (DIG_3)
/MAX7219 Dot Matrix 18/MATRIX_1-DIG_4-C4: LED18.1 (C4), U22.3 (DIG_4)
/MAX7219 Dot Matrix 18/MATRIX_1-DIG_5-C3: LED18.7 (C3), U22.10 (DIG_5)
/MAX7219 Dot Matrix 18/MATRIX_1-DIG_6-C2: LED18.2 (C2), U22.5 (DIG_6)
/MAX7219 Dot Matrix 18/MATRIX_1-DIG_7-C1: LED18.5 (C1), U22.8 (DIG_7)
/MAX7219 Dot Matrix 18/MATRIX_1-SEG_A-R2: LED18.3 (R2), U22.14 (SEG_A)
/MAX7219 Dot Matrix 18/MATRIX_1-SEG_B-R3: LED18.4 (R3), U22.16 (SEG_B)
/MAX7219 Dot Matrix 18/MATRIX_1-SEG_C-R4: LED18.10 (R4), U22.20 (SEG_C)
/MAX7219 Dot Matrix 18/MATRIX_1-SEG_D-R5: LED18.6 (R5), U22.23 (SEG_D)
/MAX7219 Dot Matrix 18/MATRIX_1-SEG_DP-R1: LED18.13 (R1), U22.22 (SEG_DP)
/MAX7219 Dot Matrix 18/MATRIX_1-SEG_E-R6: LED18.11 (R6), U22.21 (SEG_E)
/MAX7219 Dot Matrix 18/MATRIX_1-SEG_F-R7: LED18.15 (R7), U22.15 (SEG_F)
/MAX7219 Dot Matrix 18/MATRIX_1-SEG_G-R8: LED18.16 (R8), U22.17 (SEG_G)
/MAX7219 Dot Matrix 19/DOUT: J189.1 (Pin_1_1), J194.1 (Pin_1_1), U23.24 (DOUT), U24.1 (DIN)
/MAX7219 Dot Matrix 19/MATRIX_1-DIG_0-C8: LED19.9 (C8), U23.2 (DIG_0)
/MAX7219 Dot Matrix 19/MATRIX_1-DIG_1-C7: LED19.14 (C7), U23.11 (DIG_1)
/MAX7219 Dot Matrix 19/MATRIX_1-DIG_2-C6: LED19.8 (C6), U23.6 (DIG_2)
/MAX7219 Dot Matrix 19/MATRIX_1-DIG_3-C5: LED19.12 (C5), U23.7 (DIG_3)
/MAX7219 Dot Matrix 19/MATRIX_1-DIG_4-C4: LED19.1 (C4), U23.3 (DIG_4)
/MAX7219 Dot Matrix 19/MATRIX_1-DIG_5-C3: LED19.7 (C3), U23.10 (DIG_5)
/MAX7219 Dot Matrix 19/MATRIX_1-DIG_6-C2: LED19.2 (C2), U23.5 (DIG_6)
/MAX7219 Dot Matrix 19/MATRIX_1-DIG_7-C1: LED19.5 (C1), U23.8 (DIG_7)
/MAX7219 Dot Matrix 19/MATRIX_1-SEG_A-R2: LED19.3 (R2), U23.14 (SEG_A)
/MAX7219 Dot Matrix 19/MATRIX_1-SEG_B-R3: LED19.4 (R3), U23.16 (SEG_B)
/MAX7219 Dot Matrix 19/MATRIX_1-SEG_C-R4: LED19.10 (R4), U23.20 (SEG_C)
/MAX7219 Dot Matrix 19/MATRIX_1-SEG_D-R5: LED19.6 (R5), U23.23 (SEG_D)
/MAX7219 Dot Matrix 19/MATRIX_1-SEG_DP-R1: LED19.13 (R1), U23.22 (SEG_DP)
/MAX7219 Dot Matrix 19/MATRIX_1-SEG_E-R6: LED19.11 (R6), U23.21 (SEG_E)
/MAX7219 Dot Matrix 19/MATRIX_1-SEG_F-R7: LED19.15 (R7), U23.15 (SEG_F)
/MAX7219 Dot Matrix 19/MATRIX_1-SEG_G-R8: LED19.16 (R8), U23.17 (SEG_G)
/MAX7219 Dot Matrix 20/DOUT: J199.1 (Pin_1_1), J204.1 (Pin_1_1), U24.24 (DOUT), U25.1 (DIN)
/MAX7219 Dot Matrix 20/MATRIX_1-DIG_0-C8: LED20.9 (C8), U24.2 (DIG_0)
/MAX7219 Dot Matrix 20/MATRIX_1-DIG_1-C7: LED20.14 (C7), U24.11 (DIG_1)
/MAX7219 Dot Matrix 20/MATRIX_1-DIG_2-C6: LED20.8 (C6), U24.6 (DIG_2)
/MAX7219 Dot Matrix 20/MATRIX_1-DIG_3-C5: LED20.12 (C5), U24.7 (DIG_3)
/MAX7219 Dot Matrix 20/MATRIX_1-DIG_4-C4: LED20.1 (C4), U24.3 (DIG_4)
/MAX7219 Dot Matrix 20/MATRIX_1-DIG_5-C3: LED20.7 (C3), U24.10 (DIG_5)
/MAX7219 Dot Matrix 20/MATRIX_1-DIG_6-C2: LED20.2 (C2), U24.5 (DIG_6)
/MAX7219 Dot Matrix 20/MATRIX_1-DIG_7-C1: LED20.5 (C1), U24.8 (DIG_7)
/MAX7219 Dot Matrix 20/MATRIX_1-SEG_A-R2: LED20.3 (R2), U24.14 (SEG_A)
/MAX7219 Dot Matrix 20/MATRIX_1-SEG_B-R3: LED20.4 (R3), U24.16 (SEG_B)
/MAX7219 Dot Matrix 20/MATRIX_1-SEG_C-R4: LED20.10 (R4), U24.20 (SEG_C)
/MAX7219 Dot Matrix 20/MATRIX_1-SEG_D-R5: LED20.6 (R5), U24.23 (SEG_D)
/MAX7219 Dot Matrix 20/MATRIX_1-SEG_DP-R1: LED20.13 (R1), U24.22 (SEG_DP)
/MAX7219 Dot Matrix 20/MATRIX_1-SEG_E-R6: LED20.11 (R6), U24.21 (SEG_E)
/MAX7219 Dot Matrix 20/MATRIX_1-SEG_F-R7: LED20.15 (R7), U24.15 (SEG_F)
/MAX7219 Dot Matrix 20/MATRIX_1-SEG_G-R8: LED20.16 (R8), U24.17 (SEG_G)
/MAX7219 Dot Matrix 21/DOUT: J209.1 (Pin_1_1), J214.1 (Pin_1_1), U25.24 (DOUT), U26.1 (DIN)
/MAX7219 Dot Matrix 21/MATRIX_1-DIG_0-C8: LED21.9 (C8), U25.2 (DIG_0)
/MAX7219 Dot Matrix 21/MATRIX_1-DIG_1-C7: LED21.14 (C7), U25.11 (DIG_1)
/MAX7219 Dot Matrix 21/MATRIX_1-DIG_2-C6: LED21.8 (C6), U25.6 (DIG_2)
/MAX7219 Dot Matrix 21/MATRIX_1-DIG_3-C5: LED21.12 (C5), U25.7 (DIG_3)
/MAX7219 Dot Matrix 21/MATRIX_1-DIG_4-C4: LED21.1 (C4), U25.3 (DIG_4)
/MAX7219 Dot Matrix 21/MATRIX_1-DIG_5-C3: LED21.7 (C3), U25.10 (DIG_5)
/MAX7219 Dot Matrix 21/MATRIX_1-DIG_6-C2: LED21.2 (C2), U25.5 (DIG_6)
/MAX7219 Dot Matrix 21/MATRIX_1-DIG_7-C1: LED21.5 (C1), U25.8 (DIG_7)
/MAX7219 Dot Matrix 21/MATRIX_1-SEG_A-R2: LED21.3 (R2), U25.14 (SEG_A)
/MAX7219 Dot Matrix 21/MATRIX_1-SEG_B-R3: LED21.4 (R3), U25.16 (SEG_B)
/MAX7219 Dot Matrix 21/MATRIX_1-SEG_C-R4: LED21.10 (R4), U25.20 (SEG_C)
/MAX7219 Dot Matrix 21/MATRIX_1-SEG_D-R5: LED21.6 (R5), U25.23 (SEG_D)
/MAX7219 Dot Matrix 21/MATRIX_1-SEG_DP-R1: LED21.13 (R1), U25.22 (SEG_DP)
/MAX7219 Dot Matrix 21/MATRIX_1-SEG_E-R6: LED21.11 (R6), U25.21 (SEG_E)
/MAX7219 Dot Matrix 21/MATRIX_1-SEG_F-R7: LED21.15 (R7), U25.15 (SEG_F)
/MAX7219 Dot Matrix 21/MATRIX_1-SEG_G-R8: LED21.16 (R8), U25.17 (SEG_G)
/MAX7219 Dot Matrix 22/DOUT: J219.1 (Pin_1_1), J224.1 (Pin_1_1), U26.24 (DOUT), U27.1 (DIN)
/MAX7219 Dot Matrix 22/MATRIX_1-DIG_0-C8: LED22.9 (C8), U26.2 (DIG_0)
/MAX7219 Dot Matrix 22/MATRIX_1-DIG_1-C7: LED22.14 (C7), U26.11 (DIG_1)
/MAX7219 Dot Matrix 22/MATRIX_1-DIG_2-C6: LED22.8 (C6), U26.6 (DIG_2)
/MAX7219 Dot Matrix 22/MATRIX_1-DIG_3-C5: LED22.12 (C5), U26.7 (DIG_3)
/MAX7219 Dot Matrix 22/MATRIX_1-DIG_4-C4: LED22.1 (C4), U26.3 (DIG_4)
/MAX7219 Dot Matrix 22/MATRIX_1-DIG_5-C3: LED22.7 (C3), U26.10 (DIG_5)
/MAX7219 Dot Matrix 22/MATRIX_1-DIG_6-C2: LED22.2 (C2), U26.5 (DIG_6)
/MAX7219 Dot Matrix 22/MATRIX_1-DIG_7-C1: LED22.5 (C1), U26.8 (DIG_7)
/MAX7219 Dot Matrix 22/MATRIX_1-SEG_A-R2: LED22.3 (R2), U26.14 (SEG_A)
/MAX7219 Dot Matrix 22/MATRIX_1-SEG_B-R3: LED22.4 (R3), U26.16 (SEG_B)
/MAX7219 Dot Matrix 22/MATRIX_1-SEG_C-R4: LED22.10 (R4), U26.20 (SEG_C)
/MAX7219 Dot Matrix 22/MATRIX_1-SEG_D-R5: LED22.6 (R5), U26.23 (SEG_D)
/MAX7219 Dot Matrix 22/MATRIX_1-SEG_DP-R1: LED22.13 (R1), U26.22 (SEG_DP)
/MAX7219 Dot Matrix 22/MATRIX_1-SEG_E-R6: LED22.11 (R6), U26.21 (SEG_E)
/MAX7219 Dot Matrix 22/MATRIX_1-SEG_F-R7: LED22.15 (R7), U26.15 (SEG_F)
/MAX7219 Dot Matrix 22/MATRIX_1-SEG_G-R8: LED22.16 (R8), U26.17 (SEG_G)
/MAX7219 Dot Matrix 23/DOUT: J229.1 (Pin_1_1), J234.1 (Pin_1_1), U27.24 (DOUT), U28.1 (DIN)
/MAX7219 Dot Matrix 23/MATRIX_1-DIG_0-C8: LED23.9 (C8), U27.2 (DIG_0)
/MAX7219 Dot Matrix 23/MATRIX_1-DIG_1-C7: LED23.14 (C7), U27.11 (DIG_1)
/MAX7219 Dot Matrix 23/MATRIX_1-DIG_2-C6: LED23.8 (C6), U27.6 (DIG_2)
/MAX7219 Dot Matrix 23/MATRIX_1-DIG_3-C5: LED23.12 (C5), U27.7 (DIG_3)
/MAX7219 Dot Matrix 23/MATRIX_1-DIG_4-C4: LED23.1 (C4), U27.3 (DIG_4)
/MAX7219 Dot Matrix 23/MATRIX_1-DIG_5-C3: LED23.7 (C3), U27.10 (DIG_5)
/MAX7219 Dot Matrix 23/MATRIX_1-DIG_6-C2: LED23.2 (C2), U27.5 (DIG_6)
/MAX7219 Dot Matrix 23/MATRIX_1-DIG_7-C1: LED23.5 (C1), U27.8 (DIG_7)
/MAX7219 Dot Matrix 23/MATRIX_1-SEG_A-R2: LED23.3 (R2), U27.14 (SEG_A)
/MAX7219 Dot Matrix 23/MATRIX_1-SEG_B-R3: LED23.4 (R3), U27.16 (SEG_B)
/MAX7219 Dot Matrix 23/MATRIX_1-SEG_C-R4: LED23.10 (R4), U27.20 (SEG_C)
/MAX7219 Dot Matrix 23/MATRIX_1-SEG_D-R5: LED23.6 (R5), U27.23 (SEG_D)
/MAX7219 Dot Matrix 23/MATRIX_1-SEG_DP-R1: LED23.13 (R1), U27.22 (SEG_DP)
/MAX7219 Dot Matrix 23/MATRIX_1-SEG_E-R6: LED23.11 (R6), U27.21 (SEG_E)
/MAX7219 Dot Matrix 23/MATRIX_1-SEG_F-R7: LED23.15 (R7), U27.15 (SEG_F)
/MAX7219 Dot Matrix 23/MATRIX_1-SEG_G-R8: LED23.16 (R8), U27.17 (SEG_G)
/MAX7219 Dot Matrix 24/MATRIX_1-DIG_0-C8: LED24.9 (C8), U28.2 (DIG_0)
/MAX7219 Dot Matrix 24/MATRIX_1-DIG_1-C7: LED24.14 (C7), U28.11 (DIG_1)
/MAX7219 Dot Matrix 24/MATRIX_1-DIG_2-C6: LED24.8 (C6), U28.6 (DIG_2)
/MAX7219 Dot Matrix 24/MATRIX_1-DIG_3-C5: LED24.12 (C5), U28.7 (DIG_3)
/MAX7219 Dot Matrix 24/MATRIX_1-DIG_4-C4: LED24.1 (C4), U28.3 (DIG_4)
/MAX7219 Dot Matrix 24/MATRIX_1-DIG_5-C3: LED24.7 (C3), U28.10 (DIG_5)
/MAX7219 Dot Matrix 24/MATRIX_1-DIG_6-C2: LED24.2 (C2), U28.5 (DIG_6)
/MAX7219 Dot Matrix 24/MATRIX_1-DIG_7-C1: LED24.5 (C1), U28.8 (DIG_7)
/MAX7219 Dot Matrix 24/MATRIX_1-SEG_A-R2: LED24.3 (R2), U28.14 (SEG_A)
/MAX7219 Dot Matrix 24/MATRIX_1-SEG_B-R3: LED24.4 (R3), U28.16 (SEG_B)
/MAX7219 Dot Matrix 24/MATRIX_1-SEG_C-R4: LED24.10 (R4), U28.20 (SEG_C)
/MAX7219 Dot Matrix 24/MATRIX_1-SEG_D-R5: LED24.6 (R5), U28.23 (SEG_D)
/MAX7219 Dot Matrix 24/MATRIX_1-SEG_DP-R1: LED24.13 (R1), U28.22 (SEG_DP)
/MAX7219 Dot Matrix 24/MATRIX_1-SEG_E-R6: LED24.11 (R6), U28.21 (SEG_E)
/MAX7219 Dot Matrix 24/MATRIX_1-SEG_F-R7: LED24.15 (R7), U28.15 (SEG_F)
/MAX7219 Dot Matrix 24/MATRIX_1-SEG_G-R8: LED24.16 (R8), U28.17 (SEG_G)
CLK: J15.1 (Pin_1_1), J20.1 (Pin_1_1), J25.1 (Pin_1_1), J30.1 (Pin_1_1), J35.1 (Pin_1_1), J40.1 (Pin_1_1), J45.1 (Pin_1_1), J50.1 (Pin_1_1), J55.1 (Pin_1_1), J60.1 (Pin_1_1), J65.1 (Pin_1_1), J70.1 (Pin_1_1), J75.1 (Pin_1_1), J80.1 (Pin_1_1), J85.1 (Pin_1_1), J90.1 (Pin_1_1), J95.1 (Pin_1_1), J100.1 (Pin_1_1), J105.1 (Pin_1_1), J110.1 (Pin_1_1), J115.1 (Pin_1_1), J120.1 (Pin_1_1), J125.1 (Pin_1_1), J130.1 (Pin_1_1), J135.1 (Pin_1_1), J140.1 (Pin_1_1), J145.1 (Pin_1_1), J150.1 (Pin_1_1), J155.1 (Pin_1_1), J160.1 (Pin_1_1), J165.1 (Pin_1_1), J170.1 (Pin_1_1), J175.1 (Pin_1_1), J180.1 (Pin_1_1), J185.1 (Pin_1_1), J190.1 (Pin_1_1), J195.1 (Pin_1_1), J200.1 (Pin_1_1), J205.1 (Pin_1_1), J210.1 (Pin_1_1), J215.1 (Pin_1_1), J220.1 (Pin_1_1), J225.1 (Pin_1_1), J230.1 (Pin_1_1), J235.1 (Pin_1_1), J240.1 (Pin_1_1), U6.13 (CLK), U7.13 (CLK), U8.13 (CLK), U9.13 (CLK), U10.13 (CLK), U11.13 (CLK), U12.13 (CLK), U13.13 (CLK), U14.13 (CLK), U15.13 (CLK), U16.13 (CLK), U17.13 (CLK), U18.13 (CLK), U19.13 (CLK), U20.13 (CLK), U21.13 (CLK), U22.13 (CLK), U23.13 (CLK), U24.13 (CLK), U25.13 (CLK), U26.13 (CLK), U27.13 (CLK), U28.13 (CLK); also elsewhere on the board
CS: J16.1 (Pin_1_1), J21.1 (Pin_1_1), J26.1 (Pin_1_1), J31.1 (Pin_1_1), J36.1 (Pin_1_1), J41.1 (Pin_1_1), J46.1 (Pin_1_1), J51.1 (Pin_1_1), J56.1 (Pin_1_1), J61.1 (Pin_1_1), J66.1 (Pin_1_1), J71.1 (Pin_1_1), J76.1 (Pin_1_1), J81.1 (Pin_1_1), J86.1 (Pin_1_1), J91.1 (Pin_1_1), J96.1 (Pin_1_1), J101.1 (Pin_1_1), J106.1 (Pin_1_1), J111.1 (Pin_1_1), J116.1 (Pin_1_1), J121.1 (Pin_1_1), J126.1 (Pin_1_1), J131.1 (Pin_1_1), J136.1 (Pin_1_1), J141.1 (Pin_1_1), J146.1 (Pin_1_1), J151.1 (Pin_1_1), J156.1 (Pin_1_1), J161.1 (Pin_1_1), J166.1 (Pin_1_1), J171.1 (Pin_1_1), J176.1 (Pin_1_1), J181.1 (Pin_1_1), J186.1 (Pin_1_1), J191.1 (Pin_1_1), J196.1 (Pin_1_1), J201.1 (Pin_1_1), J206.1 (Pin_1_1), J211.1 (Pin_1_1), J216.1 (Pin_1_1), J221.1 (Pin_1_1), J226.1 (Pin_1_1), J231.1 (Pin_1_1), J236.1 (Pin_1_1), J241.1 (Pin_1_1), U6.12 (LOAD), U7.12 (LOAD), U8.12 (LOAD), U9.12 (LOAD), U10.12 (LOAD), U11.12 (LOAD), U12.12 (LOAD), U13.12 (LOAD), U14.12 (LOAD), U15.12 (LOAD), U16.12 (LOAD), U17.12 (LOAD), U18.12 (LOAD), U19.12 (LOAD), U20.12 (LOAD), U21.12 (LOAD), U22.12 (LOAD), U23.12 (LOAD), U24.12 (LOAD), U25.12 (LOAD), U26.12 (LOAD), U27.12 (LOAD), U28.12 (LOAD); also elsewhere on the board
DOUT: J239.1 (Pin_1_1), U28.24 (DOUT); also elsewhere on the board
GND: C12.2, C13.2, C14.2, C15.2, C16.2, C17.2, C18.2, C19.2, C20.2, C21.2, C22.2, C23.2, C24.2, C25.2, C26.2, C27.2, C28.2, C29.2, C30.2, C31.2, C32.2, C33.2, C34.2, J17.1 (Pin_1_1), J22.1 (Pin_1_1), J27.1 (Pin_1_1), J32.1 (Pin_1_1), J37.1 (Pin_1_1), J42.1 (Pin_1_1), J47.1 (Pin_1_1), J52.1 (Pin_1_1), J57.1 (Pin_1_1), J62.1 (Pin_1_1), J67.1 (Pin_1_1), J72.1 (Pin_1_1), J77.1 (Pin_1_1), J82.1 (Pin_1_1), J87.1 (Pin_1_1), J92.1 (Pin_1_1), J97.1 (Pin_1_1), J102.1 (Pin_1_1), J107.1 (Pin_1_1), J112.1 (Pin_1_1), J117.1 (Pin_1_1), J122.1 (Pin_1_1), J127.1 (Pin_1_1), J132.1 (Pin_1_1), J137.1 (Pin_1_1), J142.1 (Pin_1_1), J147.1 (Pin_1_1), J152.1 (Pin_1_1), J157.1 (Pin_1_1), J162.1 (Pin_1_1), J167.1 (Pin_1_1), J172.1 (Pin_1_1), J177.1 (Pin_1_1), J182.1 (Pin_1_1), J187.1 (Pin_1_1), J192.1 (Pin_1_1), J197.1 (Pin_1_1), J202.1 (Pin_1_1), J207.1 (Pin_1_1), J212.1 (Pin_1_1), J217.1 (Pin_1_1), J222.1 (Pin_1_1), J227.1 (Pin_1_1), J232.1 (Pin_1_1), J237.1 (Pin_1_1), J242.1 (Pin_1_1), U6.4 (GND), U6.9 (GND), U7.4 (GND), U7.9 (GND), U8.4 (GND), U8.9 (GND), U9.4 (GND), U9.9 (GND), U10.4 (GND), U10.9 (GND), U11.4 (GND), U11.9 (GND), U12.4 (GND), U12.9 (GND), U13.4 (GND), U13.9 (GND), U14.4 (GND), U14.9 (GND), U15.4 (GND), U15.9 (GND), U16.4 (GND), U16.9 (GND), U17.4 (GND), U17.9 (GND), U18.4 (GND), U18.9 (GND)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; also elsewhere on the board
unnamed: R12.2, U6.18 (ISET)
unnamed: R13.2, U7.18 (ISET)
unnamed: R14.2, U8.18 (ISET)
unnamed: R15.2, U9.18 (ISET)
unnamed: R16.2, U10.18 (ISET)
unnamed: R17.2, U11.18 (ISET)
unnamed: R18.2, U12.18 (ISET)
unnamed: R19.2, U13.18 (ISET)
unnamed: R20.2, U14.18 (ISET)
unnamed: R21.2, U15.18 (ISET)
unnamed: R22.2, U16.18 (ISET)
unnamed: R23.2, U17.18 (ISET)
unnamed: R24.2, U18.18 (ISET)
unnamed: R25.2, U19.18 (ISET)
unnamed: R26.2, U20.18 (ISET)
unnamed: R27.2, U21.18 (ISET)
unnamed: R28.2, U22.18 (ISET)
unnamed: R29.2, U23.18 (ISET)
unnamed: R30.2, U24.18 (ISET)
unnamed: R31.2, U25.18 (ISET)
unnamed: R32.2, U26.18 (ISET)
unnamed: R33.2, U27.18 (ISET)
unnamed: R34.2, U28.18 (ISET)
